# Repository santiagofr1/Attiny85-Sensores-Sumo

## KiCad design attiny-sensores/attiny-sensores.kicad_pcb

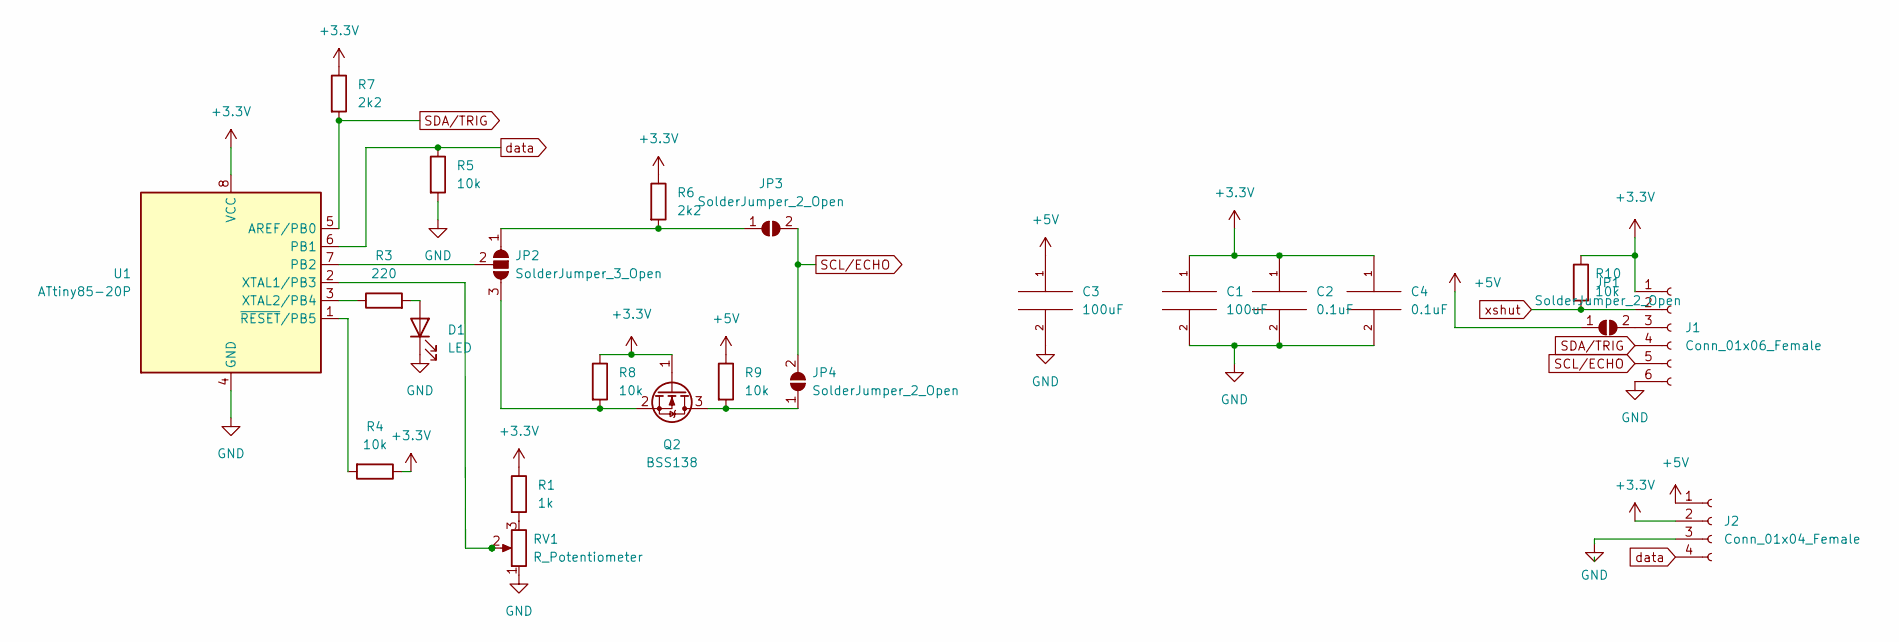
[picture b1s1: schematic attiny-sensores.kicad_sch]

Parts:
C1, C3: 100uF; CP_Elec_6.3x5.3
C2, C4: 0.1uF; C_0805_2012Metric_Pad1.18x1.45mm_HandSolder
D1: LED; LED_0805_2012Metric_Pad1.15x1.40mm_HandSolder
J1: Conn_01x06_Female; PinHeader_1x06_P2.54mm_Vertical
J2: Conn_01x04_Female; PinSocket_1x04_P2.54mm_Vertical
JP1, JP3, JP4: SolderJumper_2_Open; SolderJumper-2_P1.3mm_Open_TrianglePad1.0x1.5mm
JP2: SolderJumper_3_Open; SolderJumper-3_P2.0mm_Open_TrianglePad1.0x1.5mm
Q2: BSS138; SOT-23
R1: 1k; R_0805_2012Metric_Pad1.20x1.40mm_HandSolder
R3: 220; R_0805_2012Metric_Pad1.20x1.40mm_HandSolder
R4, R5, R8, R9, R10: 10k; R_0805_2012Metric_Pad1.20x1.40mm_HandSolder
R6, R7: 2k2; R_0805_2012Metric_Pad1.20x1.40mm_HandSolder
RV1: R_Potentiometer; Potentiometer_Bourns_3266Y_Vertical
U1: ATtiny85-20P; DIP-8_W7.62mm

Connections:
+3.3V: C1.1, C2.1, C4.1, J1.1, J2.2, Q2.1 (G), R1.1, R4.1, R6.1, R7.1, R8.1, R10.1, U1.8 (VCC)
+5V: C3.1, J2.1, JP1.1 (A), R9.1
GND: C1.2, C2.2, C3.2, C4.2, D1.1 (K), J1.6, J2.3, R5.2, RV1.1, U1.4 (GND)
unnamed: D1.2 (A), R3.2
unnamed: J1.3, JP1.2 (B)
unnamed: JP2.1 (A), JP3.1 (A), R6.2
unnamed: JP2.2 (C), U1.7 (PB2)
unnamed: JP2.3 (B), Q2.2 (S), R8.2
unnamed: JP4.1 (A), Q2.3 (D), R9.2
unnamed: R3.1, U1.3 (XTAL2/PB4)
unnamed: R4.2, U1.1 (~RESET/PB5)
unnamed: RV1.2, U1.2 (XTAL1/PB3)
unnamed: R1.2, RV1.3
SCL/ECHO: J1.5, JP3.2 (B), JP4.2 (B)
SDA/TRIG: J1.4, R7.2, U1.5 (AREF/PB0)
data: J2.4, R5.1, U1.6 (PB1)
xshut: J1.2, R10.2

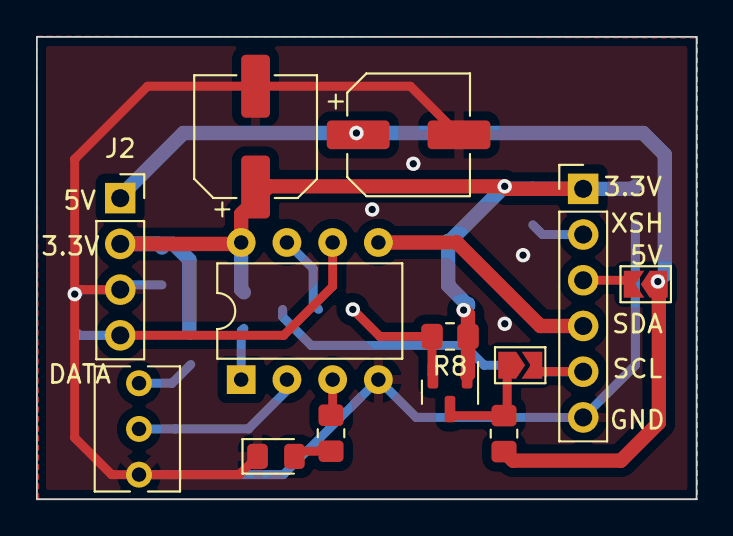
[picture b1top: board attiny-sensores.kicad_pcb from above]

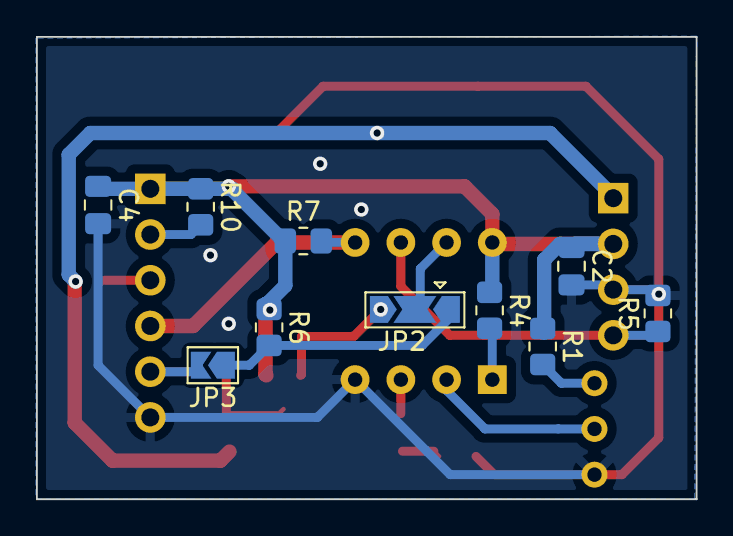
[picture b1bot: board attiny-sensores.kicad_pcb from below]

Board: 2 copper layers, 36.6 x 25.7 mm, 23 parts (10 on the bottom side), 17 nets.
